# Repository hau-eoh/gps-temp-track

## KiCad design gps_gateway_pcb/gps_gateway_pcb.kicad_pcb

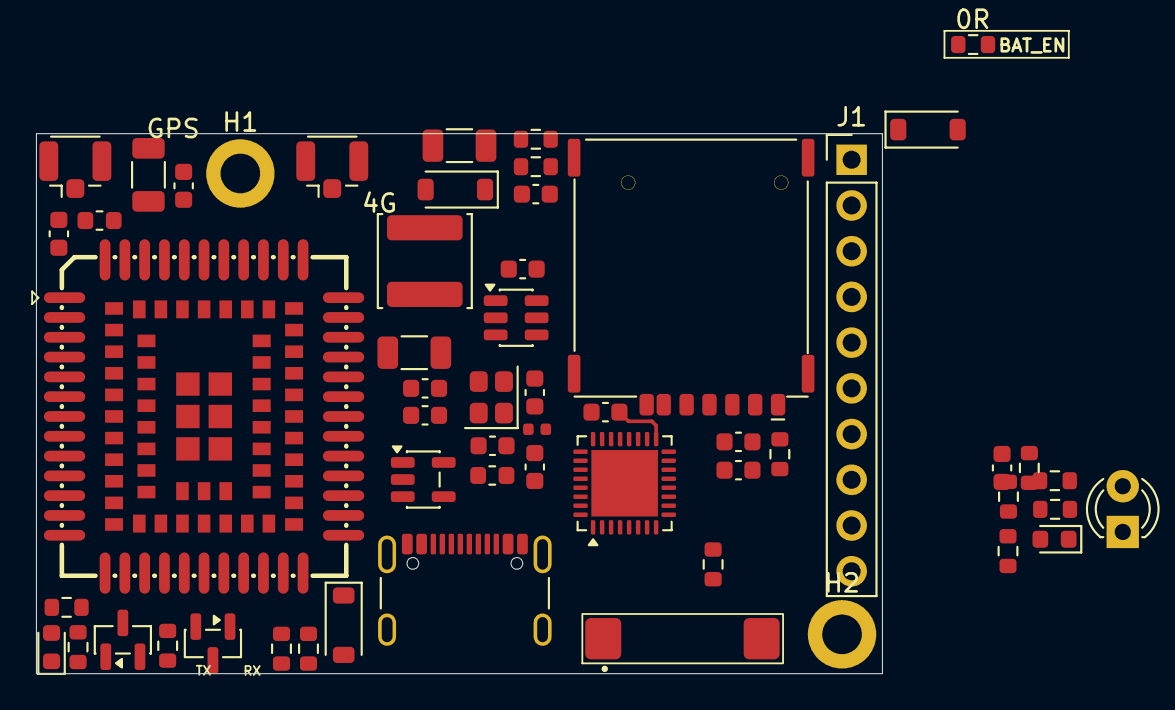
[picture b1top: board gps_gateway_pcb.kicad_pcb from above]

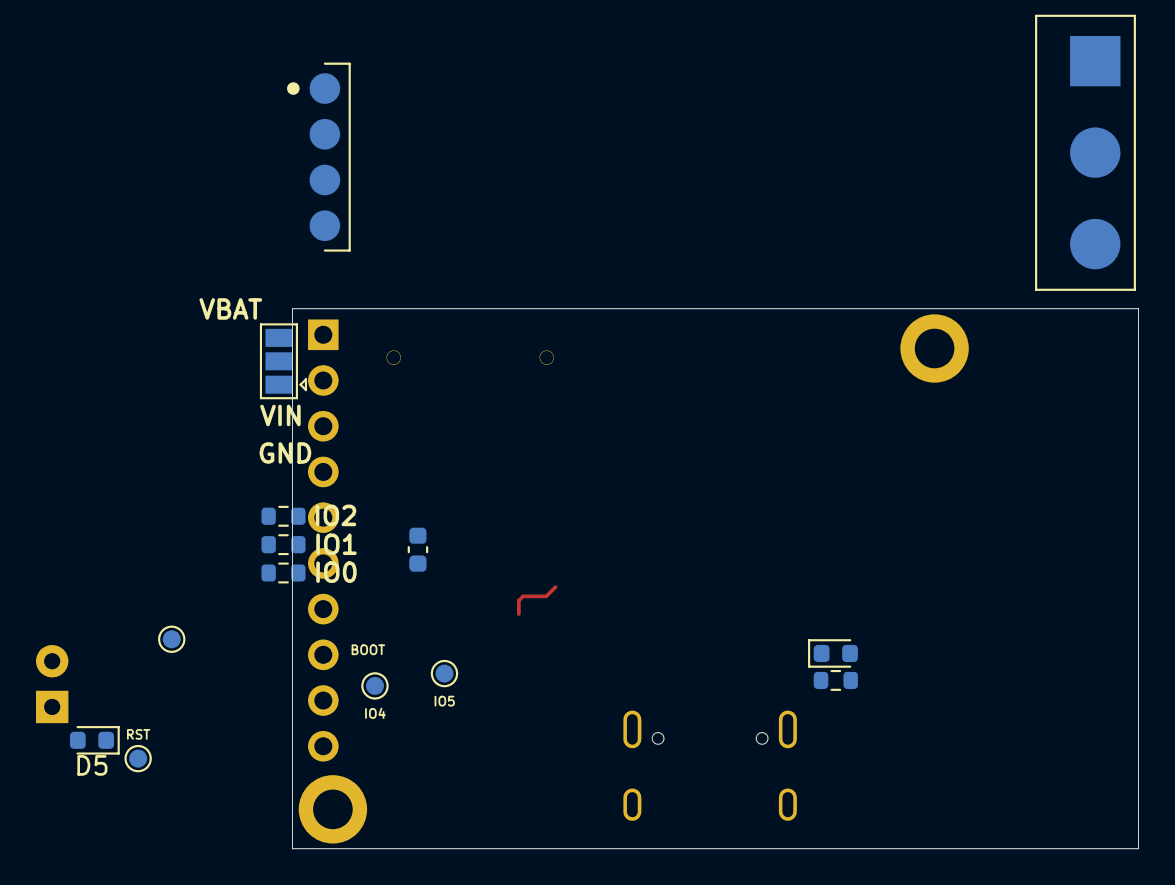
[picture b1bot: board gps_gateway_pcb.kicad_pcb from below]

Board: 2 copper layers, 47.0 x 30.0 mm, 69 parts (13 on the bottom side), 49 nets.

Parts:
AE1: Antenna_Chip; Anten AN9520 Rainsun 2.4G
C1, C6: 10uF; C_0603_1608Metric
C3, C5, C7, C12, C14: 0.1uF; C_0603_1608Metric
C4: 10nF; C_0603_1608Metric
C8: 1uF; C_0603_1608Metric
C9: 56pF; C_0603_1608Metric
C13, C15: 47uF; C_1206_3216Metric
C17, C18: 10pF; C_0603_1608Metric
C21: 10uF; C_1206_3216Metric
C23: 100pF; C_0603_1608Metric
C27: 100nF; C_0603_1608Metric
D1, D2, D3: 1N5819W; D_SOD-123
D4: PW; LED_0603_1608Metric
D5, D7: ST; LED_0603_1608Metric
D6: LED; LED_D3.0mm
D8: NET; LED_0603_1608Metric
H1, H2: MountingHole_Pad; MountingHole_2.2mm_M2_DIN965_Pad
J1: Conn_01x10_Pin; PinHeader_1x10_P2.54mm_Vertical
J3: GNSS; U.FL_Hirose_U.FL-R-SMT-1_Vertical
J4: USB_OTG; USB_C_Receptacle_GCT_USB4105-xx-A_16P_TopMnt_Horizontal
J5: 4G; U.FL_Hirose_U.FL-R-SMT-1_Vertical
J6: EG800; EC800E-CN
J7: SIM_Card; nanoSIM_ConnMold_CMNSM661004
JP1: SolderJumper_3_Open; SolderJumper-3_P1.3mm_Open_Pad1.0x1.5mm
L1: 2.2nH; L_0603_1608Metric
L2: 4.7uH; L_APV_ANR5040
L3: 24nH; L_0402_1005Metric
L4: VHF160808H47NJT; L_0603_1608Metric
M1: RS485; Module TTL to RS485 SMD
Q2, Q3: SS8050; SOT-23
R1: 0R; R_0603_1608Metric
R2: 100K; R_0603_1608Metric
R3, R9, R12, R13, R17, R18: 4K7; R_0603_1608Metric
R5: 16K9; R_0603_1608Metric
R6, R7, R8, R10, R15, R16, R21, R24, R25, R26: 10K; R_0603_1608Metric
TP1: IO5; TestPoint_Pad_D1.0mm
TP2: IO4; TestPoint_Pad_D1.0mm
TP3: RST; TestPoint_Pad_D1.0mm
TP4: BOOT; TestPoint_Pad_D1.0mm
U2: TPS54202DDC; SOT-23-6
U3: ESP32-C3FH4; QFN-32-1EP_5x5mm_P0.5mm_EP3.7x3.7mm
U4: RT9013-33GB; TSOT-23-5
Y1: 40MHz; Crystal_SMD_2520-4Pin_2.5x2.0mm

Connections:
/ADC_CURENT: C14.2, R8.2, R10.1, U3.8 (GPIO3)
/AT_GNSS: C23.2, J6.2 (AT_GNSS)
/BOOT: R7.1, TP4.1, U3.15 (GPIO9)
/ESP_RX_SIM: Q3.3 (C), R16.1, U3.27 (U0RXD)
/ESP_TX_SIM: Q2.2 (E), U3.28 (U0TXD)
/IO0: J1.6, M1.3 (RXD), R26.2, U3.4 (XTAL_32K_P)
/IO1: J1.5, M1.2 (TXD), R25.2, U3.5 (XTAL_32K_N)
/IO2: J1.4, R24.2, U3.6 (GPIO2)
/IO4: TP2.1, U3.9 (MTMS)
/IO5: TP1.1, U3.10 (MTDI)
/MCU_SIM_KEY: J6.7 (PWRKEY), U3.13 (MTDO)
/NET_STATUS: D8.1 (K), J6.16 (NET_STATUS)
/RST: R6.1, TP3.1, U3.7 (CHIP_EN)
/SIM_MAIN_RX: J6.17 (MAIN_RX), Q2.3 (C), R15.1
/SIM_MAIN_TX: J6.18 (MAIN_TX), Q3.2 (E)
/SIM_STATUS: D7.1 (K), J6.25 (STATUS)
/Status: R9.1, U3.12 (MTCK)
/USB_DN: J4.A7 (D-), J4.B7 (D-), U3.25 (GPIO18)
/USB_DP: J4.A6 (D+), J4.B6 (D+), U3.26 (GPIO19)
/USIM_CLK: J6.13 (USIM1_CLK), J7.C3 (CLK)
/USIM_DATA: J6.11 (USIM1_DATA), J7.C7 (I/O), R21.1
/USIM_RST: J6.12 (USIM1_RST), J7.C2 (RST)
/USIM_VDD: C27.2, J6.14 (USIM1_VDD), J7.C1 (VCC), R21.2
/VCC5: D1.2 (A), J4.A4 (VBUS), J4.A9 (VBUS), J4.B4 (VBUS), J4.B9 (VBUS)
/VDD_EXT: J6.24 (VDD_EXT), R15.2, R17.2, R18.2
GND: AE1.2 (PCB_Trace), C1.2, C3.2, C4.2, C6.2, C7.2, C8.2, C12.1, C13.1, C14.1, C15.1, C17.1, C18.1, C21.1, C27.1, D4.1 (K), D5.1 (K), D6.1 (K), H1.1, H2.1, J1.3, J3.2 (Ext), J4.A1 (GND), J4.A12 (GND), J4.B1 (GND), J4.B12 (GND), J4.S1 (SHIELD), J5.2 (Ext), J6.1 (GND1), J6.10 (GND2), J6.27 (GND4), J6.34 (GND20), J6.36 (GND6), J6.37 (GND7), J6.40 (GND8), J6.41 (GND9), J6.45 (GND10), J6.46 (GND11), J6.47 (GND12), J6.48 (GND13), J6.70 (GND14), J6.71 (GND15), J6.72 (GND16), J6.73 (GND17), J6.88 (GND18), J6.89 (GND19), J6.90 (GND20), J6.91 (GND21), J6.92 (GND22), J6.93 (GND33), J6.94 (GND24), J6.95 (GND3), J7.C5 (GND), J7.SH, M1.4 (GND), M1.7 (E), R5.2, R10.2, U2.1 (GND), U3.33 (GND), U4.2 (GND), Y1.2, Y1.4
unnamed: AE1.1 (FEED), U3.1 (LNA_IN)
unnamed: C8.1, L1.2, U3.2 (VDD3P3), U3.3 (VDD3P3)
unnamed: C18.2, L3.1, Y1.1
unnamed: D1.1 (K), D2.1 (K), U2.3 (VIN)
unnamed: D2.2 (A), J1.2, JP1.1 (A)
unnamed: D3.2 (A), L2.2
unnamed: D4.2 (A), R3.2
unnamed: D5.2 (A), D6.2 (A), R9.2
unnamed: D7.2 (A), R12.1
unnamed: D8.2 (A), R13.1
unnamed: J1.1, JP1.3 (B)
unnamed: C23.1, J3.1 (In), L4.1
unnamed: J5.1 (In), J6.35 (ANNT_MAIN)
unnamed: Q2.1 (B), R17.1
unnamed: Q3.1 (B), R18.1
unnamed: C5.2, U2.6 (BOOT)
unnamed: C9.2, R2.2, R5.1, U2.4 (FB)
unnamed: C5.1, L2.1, U2.2 (SW)
unnamed: C17.2, U3.29 (XTAL_N), Y1.3
unnamed: L3.2, U3.30 (XTAL_P)
SIM_VBAT: C9.1, C12.2, C13.2, C21.2, D3.1 (K), J6.42 (VBAT1), J6.43 (VBAT2), L4.2, R1.1, R2.1, R13.2, R16.2, U4.1 (VIN)
VCC33: C1.1, C3.1, C4.1, C6.1, C7.1, C15.2, L1.1, M1.1 (VCC), R3.1, R6.2, R7.2, R12.2, R24.1, R25.1, R26.1, U3.11 (VDD3P3_RTC), U3.17 (VDD3P3_CPU), U3.31 (VDDA), U3.32 (VDDA), U4.5 (VOUT)
VOL_CHECK: JP1.2 (C), R1.2, R8.1

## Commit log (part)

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2025-12-24 add history data
2025-12-24 update point maker on tracking line
2025-12-24 update 0, 0 value skip
2025-12-24 Update title and improve JSON parsing logic
2026-01-06 add bat and collapse popup
2026-01-06 Increase mobileHeight from 600 to 1200
2026-01-06 Adjust mobileHeight for better responsiveness
2026-01-06 Change mobileHeight to 900 and init icon menu
    Updated mobileHeight to 900 and initialized icon menu.
2026-01-06 Move eraWidget initialization to map setup
2026-01-14 add map menu change style
2026-01-14 Update print statement to say 'Goodbye World'
2026-01-14 Modify quick select options and add distance calculation
    Updated the quick select options and changed the current icon type to 'arrow'. Added total distance calculation and updated status text to include distance in kilometers.
2026-01-15 init project
2026-01-21 layout done go to prototype
2026-01-30 add ttl2rs485 module
2026-02-02 optimize pcb
2026-03-30 change size
